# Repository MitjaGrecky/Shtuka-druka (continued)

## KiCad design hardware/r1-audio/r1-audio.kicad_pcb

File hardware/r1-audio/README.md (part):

# R1 - Audio board (rear wall, left: Audio Out and Audio In blocks)

The audio jacks and the analog front end. Every input leaves R1 as a differential pair scaled to the converters' full scale;
the Cirrus buffers around ADC_VMID / DAC_VMID (AN0635 for the CS5304P/8P inputs, AN0679 for the CS4308P outputs) sit next to the
converters on A1. Research: `docs/ru/34_rear_boards_research.md` (sections 2, 3), doc 28. Decisions: R64-R66, R72, R88,
R116-R118, R135-R137, R142 (jack positions = 3D model).

**Rev 1.4 (25.11.2026, P154):** "to F1" PH 3 -> 5 pins (DET_HP1/2), new PH-3 "HP detect to R2".
**Status: rev 1.3 (20.11.2026) - schematic and placed board, not routed; decision P114 (20.11.2026): 6 layers (F sig / In1 GND / In2 sig / In3 sig / In4 GND / B sig), generator change pending, pin rule not yet applied; changes in the Rev sections below.** Rev 0.8 (18.11.2026): 452 parts, 264 nets; Mic/Line attenuator relays since rev 0.3, user decision on В16). Levels and values checked against the datasheets (cloud task #24).

## Channels

| Input | Jack | Path | ADC (A1) |
|---|---|---|---|
| Mic/Line 1-2 | Neutrik NCJ6FI-V combo, vertical (not at JLC: hand soldering, P122; the LCSC number is outdated) | phantom 6.81k + 47 uF on XLR only (R72); TRS joins after the caps; clamps to +-12 V; relay attenuator -12 dB (rev 0.3); OPA1612 two-op-amp front end x 4.01; OPA1637 loud x 0.681 (FS +11.9 dBu) and quiet x 68.1 (+40 dB, FS -28.1 dBu) | 1-4 (two per input, R117) |
| Hi-Z 1-2 | Neutrik NJ3FD-V, vertical | 1 MOhm, clamps, OPA1642 buffer; OPA1637 loud x 1.37 (FS +17.9 dBu), quiet x 137 (+40 dB, FS -22.1 dBu) | 5-8 |
| Phono L/R | RCA with nut (part to choose) | relay per channel (R118; off = line): line -> OPA1637 x 4.12 (FS +8.3 dBu); phono -> computed RIAA on OPA1612 (+35 dB at 1 kHz) -> OPA1637 x 4.12 | 9-10 |
| Line 1-8 | NJ3FD-V | RF filter, OPA1637 diff x 0.674: FS +24.1 dBu (R135) | 11-18 |
| Spare (R88) | - | on A1 | 19-20 |

| Output | Path |
|---|---|
| Main L/R, Aux L/R (NJ3FD-V) | DAC pair (2 Vrms diff from the A1 I-V stage) -> OPA1612 difference amp x 3.09 -> 6.19 Vrms = +18.0 dBu (R64); hot through 47 R, cold 47 R to GND (impedance-balanced) |
| RCA L/R | copy of Main through 100 R (R23) |
| Relays | Omron G6K-2F-Y 5 V, one DPDT per pair (Main, Aux, RCA): normally open, close only when MUTE and R2_OK are high (R66, R137, R118) |

Phantom per channel (R118): MMBTA92 (300 V PNP) high-side switch from +48 V, slow ramp by a Miller capacitor (2.2 uF base-collector), driven from R2 through an
MMBTA42 (300 V NPN, the collector sees 48 V); 47k bleeder.

Connectors: power from PW (Micro-Fit 2x5, same pinout as PW "to A1/R1"), control from R2 (2x7: the 2x5 pinout of R2 "to A1/R1" plus ATT1 at pin 11 and ATT2 at pin 13, GND between; R2 must be widened - PC task #25),
to A1: 2x20 (ADC 1-10) and 2x25 (ADC 11-18, DAC 1-4, +-12 V, +5 V) - pairs on adjacent pins with GND pairs between.

## Level plan (checked, rev 0.2)

Sources: CS53A04P datasheet DS1397 (same family as CS5304P/8P), CS4308P DS1317, Cirrus AN0635 and AN0679.

- **ADC:** 0 dBFS = 2.0 Vrms differential at the ADC pins (scales with VDD_A). The recommended AN0635 input buffer (inverting, 1.2k in /
  300 R feedback, 68 uF per leg, OPA1612) has gain 1/4: 0 dBFS = **8 Vrms differential** at the buffer. Rev 0.1 assumed 2 Vrms - every
  gain is now x 4.17 higher. With the 49.9 R build-out the R1 driver must deliver 8.33 Vrms differential at full scale.
  The 49.9 R + 1 nF filter: 1.6 MHz differential, fine ahead of the buffer's own 640 kHz filter; C0G.
- **Line 1-8:** gain 6.81k / (10k + 100 R) = 0.674, FS at +24.1 dBu (R135). Input 100 R + 1 nF (RF, 1.6 MHz). No clamps (a clamp to +-12 V
  would clip +24 dBu = 17 Vpk); the OPA1637 inputs see only the Rg current.
- **Mic/Line:** front end 1 + 2 x 499 / 332 = 4.01 (+12 dB) - the 332 R gives thermal noise 2.3 nV/rtHz instead of 3.3 with 665 R. The front end clips at
  about +13.6 dBu (+-10.5 V on each output), so FS of the loud path is set to +11.9 dBu: **no pad is needed**, the loud path has 1.7 dB headroom
  over line level; a line signal above +13.6 dBu on the combo clips (question to the user). Quiet path +40 dB higher, FS -28.1 dBu; the 1k Rg
  keeps the fault current into the OPA1637 below 10 mA.
- **Attenuator (rev 0.3, В16 b):** one G6K-2F-Y per combo after the phantom caps and the 10 R, in front of the clamps and the front end: 15k series + 4.99k shunt per leg
  (ratio 0.250 = -12.0 dB, 0.1 %). De-energised = direct (mic), energised = attenuated: FS of the loud path +23.9 dBu; the clamps see
  only the attenuated signal. Control: ATT1/ATT2 from R2 (3.3 V) through a 2N7002, flyback diode per coil. In the direct position the divider loads each leg with 20k
  (parallel to the 10k bias: 6.7k per leg, 13 k differential) - fine for microphones; the divider adds 7.8 nV/rtHz only while attenuated.
- **Hi-Z:** OPA1642 buffer, then x 1.37 / x 137 (FS +17.9 / -22.1 dBu). The JFET buffer keeps the 1 MOhm input.
- **Phono:** FS of the line path +8.3 dBu (2.02 Vrms, CD level). RIAA computed (script in the cloud task, `docs/ru/` note): active stage 3180 / 318 us
  (68.1k || 47n in series with 7.42k, over 130 R + 470 uF), 75 us as a passive section 787 R + 100 nF ahead of the FDA (input 16.7 k).
  Gain +35.0 dB at 1 kHz, **error below 0.05 dB from 20 Hz to 20 kHz** (nominal values), FS 36 mV at 1 kHz (7 x the 5 mV of a normal MM
  cartridge); corner of the 130 R + 470 uF leg 2.6 Hz (the subsonic rolloff is left to the DSP). 0.1 % resistors and 1 % C0G capacitors give
  about +-0.1 dB.
- **Outputs:** CS4308P current-mode output 1.67 mA rms (1.63-1.71) per channel; AN0679 I-V stage 1.2 kOhm gives 2.0 Vrms differential
  (the A1 stage, not R1). R1: x 3.09 -> 6.19 Vrms = +18.0 dBu per channel, impedance-balanced (cold 47 R).
- **Phantom:** MMBTA92 + Miller capacitor 2.2 uF between base and collector: base current 0.45 mA from the 100k, ramp about 0.1-0.2 s
  (X7R loses capacity at 48 V, 1-2 uF effective); Vce(sat) < 0.5 V at 14 mA (both legs shorted); turn-off through the 100k pull-up
  and the 47k bleeder. Estimated, not simulated. The level shifter is the MMBTA42 (300 V): the old MMBT3904 (40 V) sees 48 V on its
  collector when off.

## Still open

- Mic EIN: front end 2.3 nV/rtHz plus the 6.81k phantom resistors (about 3.3 nV/rtHz each in parallel to the capsule) - about -125 dBu EIN estimated,
  to measure on the first board; the quiet path reaches ADC FS at -28.1 dBu, so the ADC noise floor (123 dBA) is -95 dBu referred to the input.
- Jack mechanics: vertical-mount NCJ6FI-V and NJ3FD-V on a vertical board; RCA part; positions from the 3D model.
- Model vs R118: the model shows a Phono/Line switch on the wall, R118 says R2 switches phono/line (relays here).
- The A1 buffers (AN0635, AN0679) are on A1: R1 only assumes them.

Rev 0.4 (14.11.2026, PC): JST PH 3 "to F1 (mute)" with MUTE, R2_OK, GND for the headphone board.

Checks: `tools/sch_netcheck.py hardware/r1-audio` - 440 symbol units, 1159 pins, 0 mismatches; every symbol pin listed.
ERC by CI. OPA1637 symbol: project library (`hardware/m1-screen-knobs/gen/make_lib.py`, `opa1637()`).

Generators: `gen/design.py`, `gen/make_sch.py`. On the PC set `KICAD_SYMBOL_DIR=<repo>/hardware/common/sym7`.

License: CERN-OHL-S-2.0 (hardware), AGPL-3.0-or-later (scripts).

## Rev 0.5: placed board for routing (14.11.2026, PC)
Placed board (no routing) generated by `gen/make_pcb.py`; `UNROUTED` marker for CI; package `hardware/for-routing/R1`. Placement is a starting point: jacks at the 3D-model positions, the rest by `hardware/common/gen/autoplace.py` (ICs on a grid, small parts around the IC they share signals with, cable headers along the bottom edge). Outline and mounting holes are rough until the enclosure is fixed. `pcb_geomcheck`: 0 problems.

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
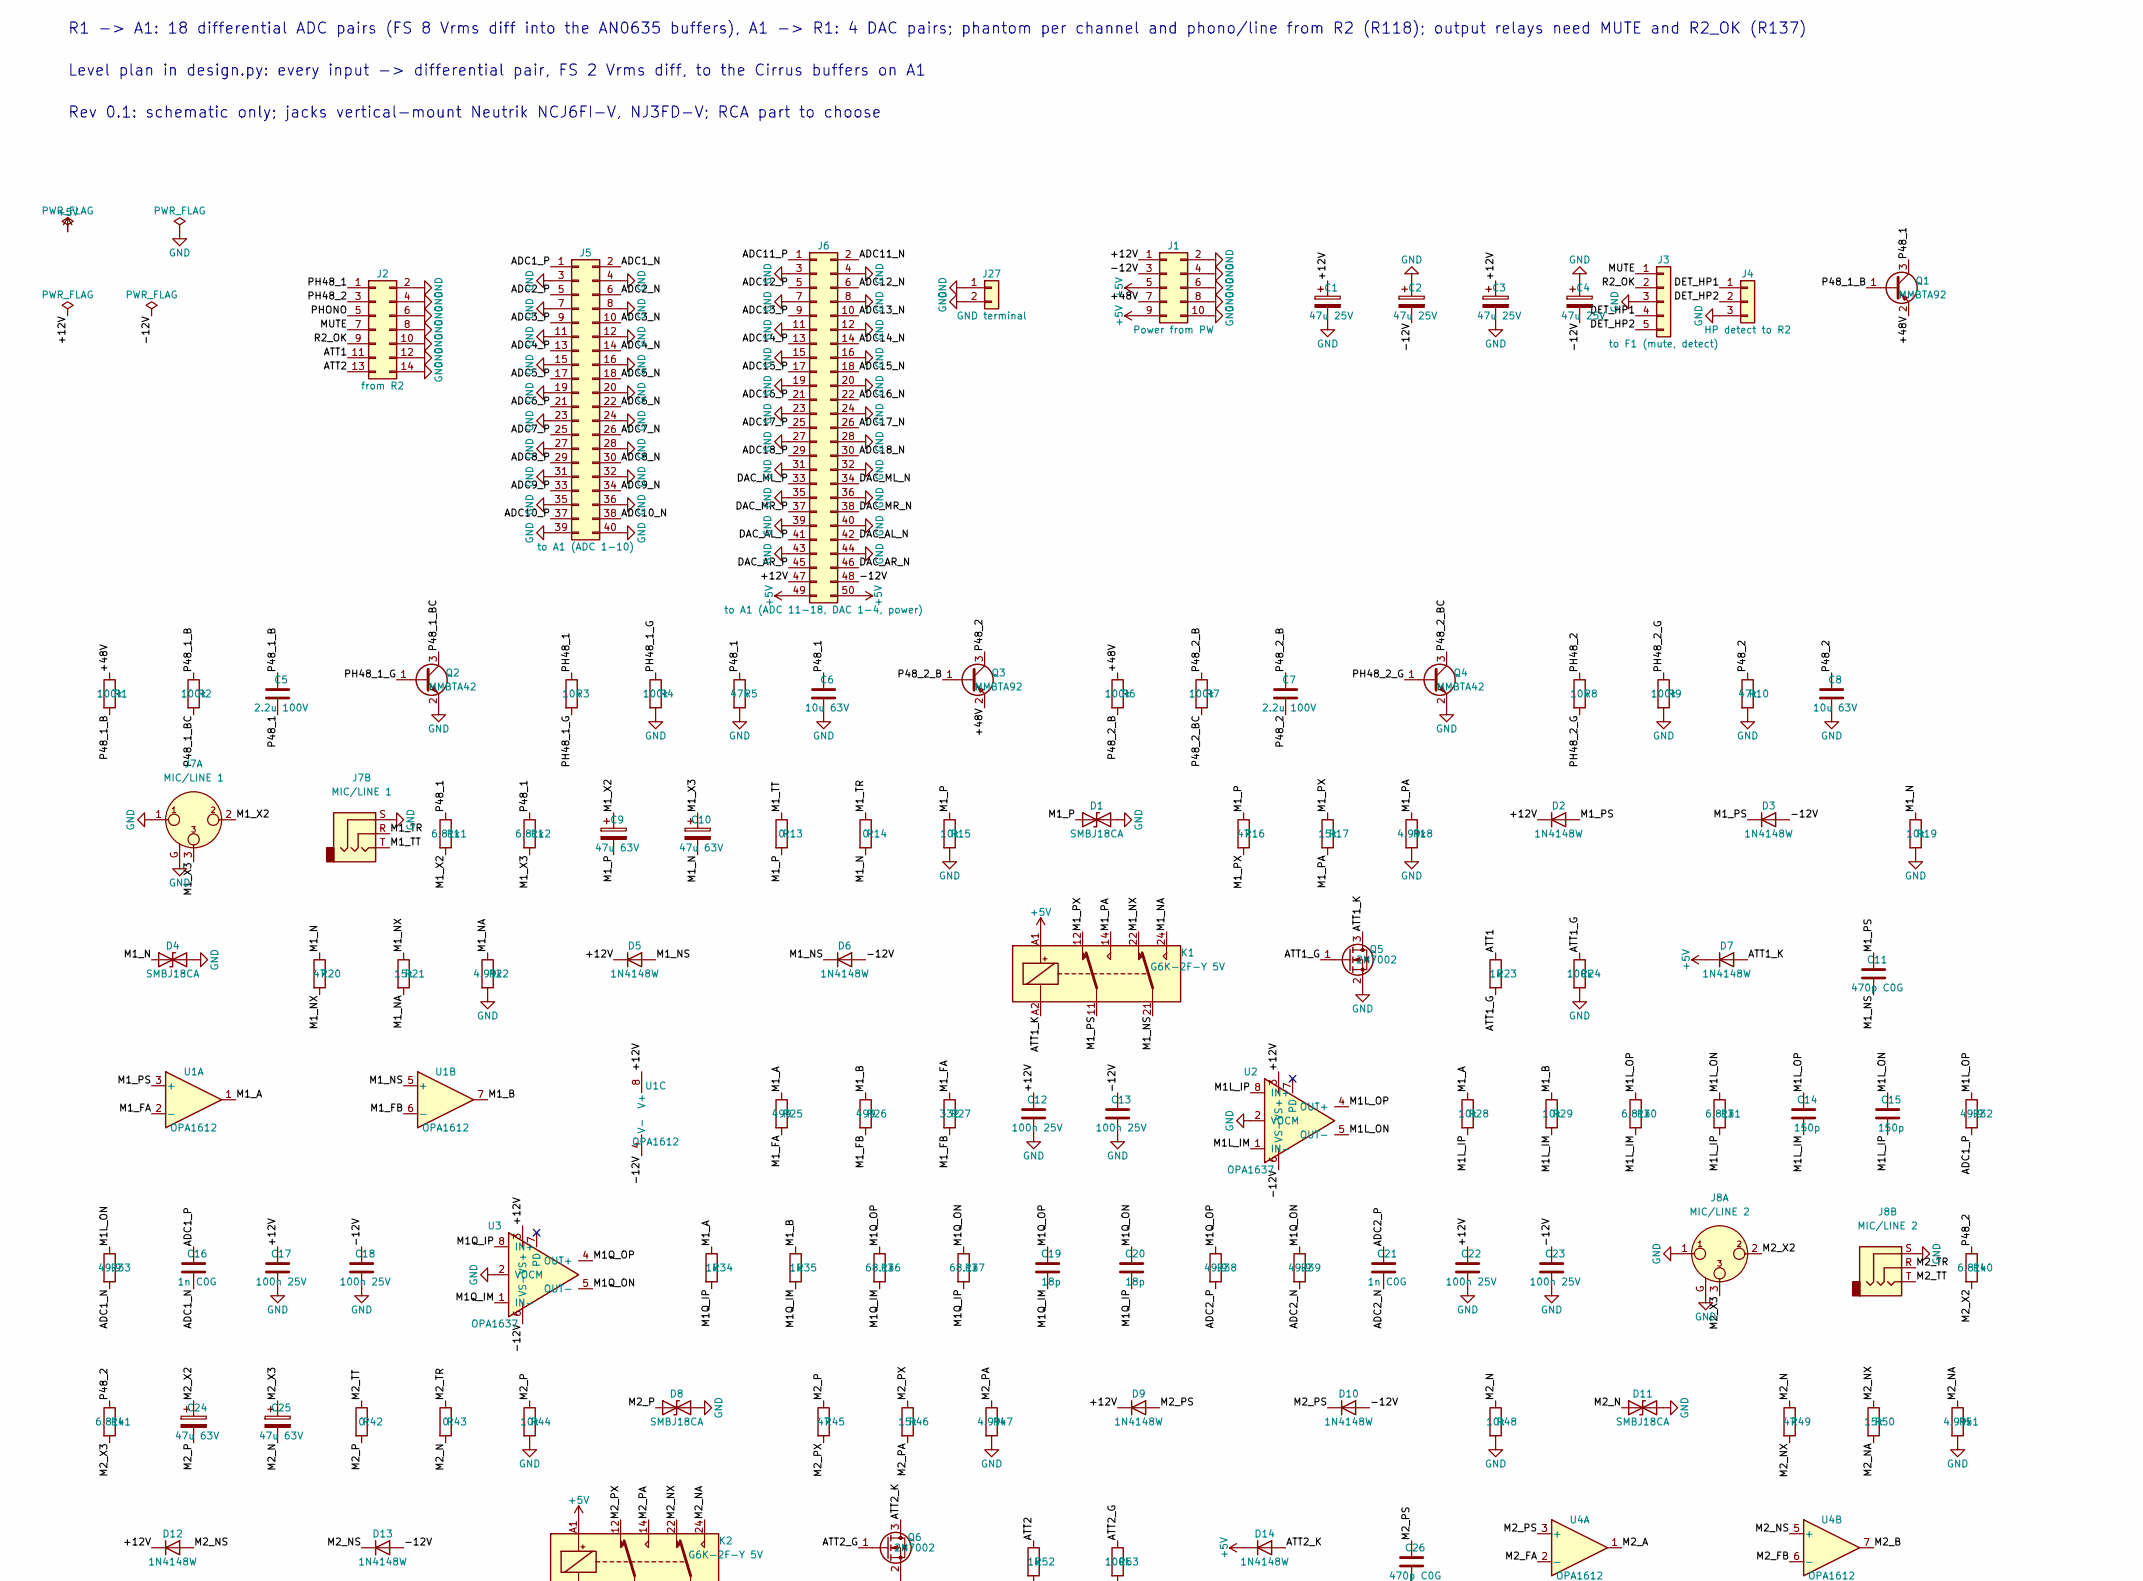
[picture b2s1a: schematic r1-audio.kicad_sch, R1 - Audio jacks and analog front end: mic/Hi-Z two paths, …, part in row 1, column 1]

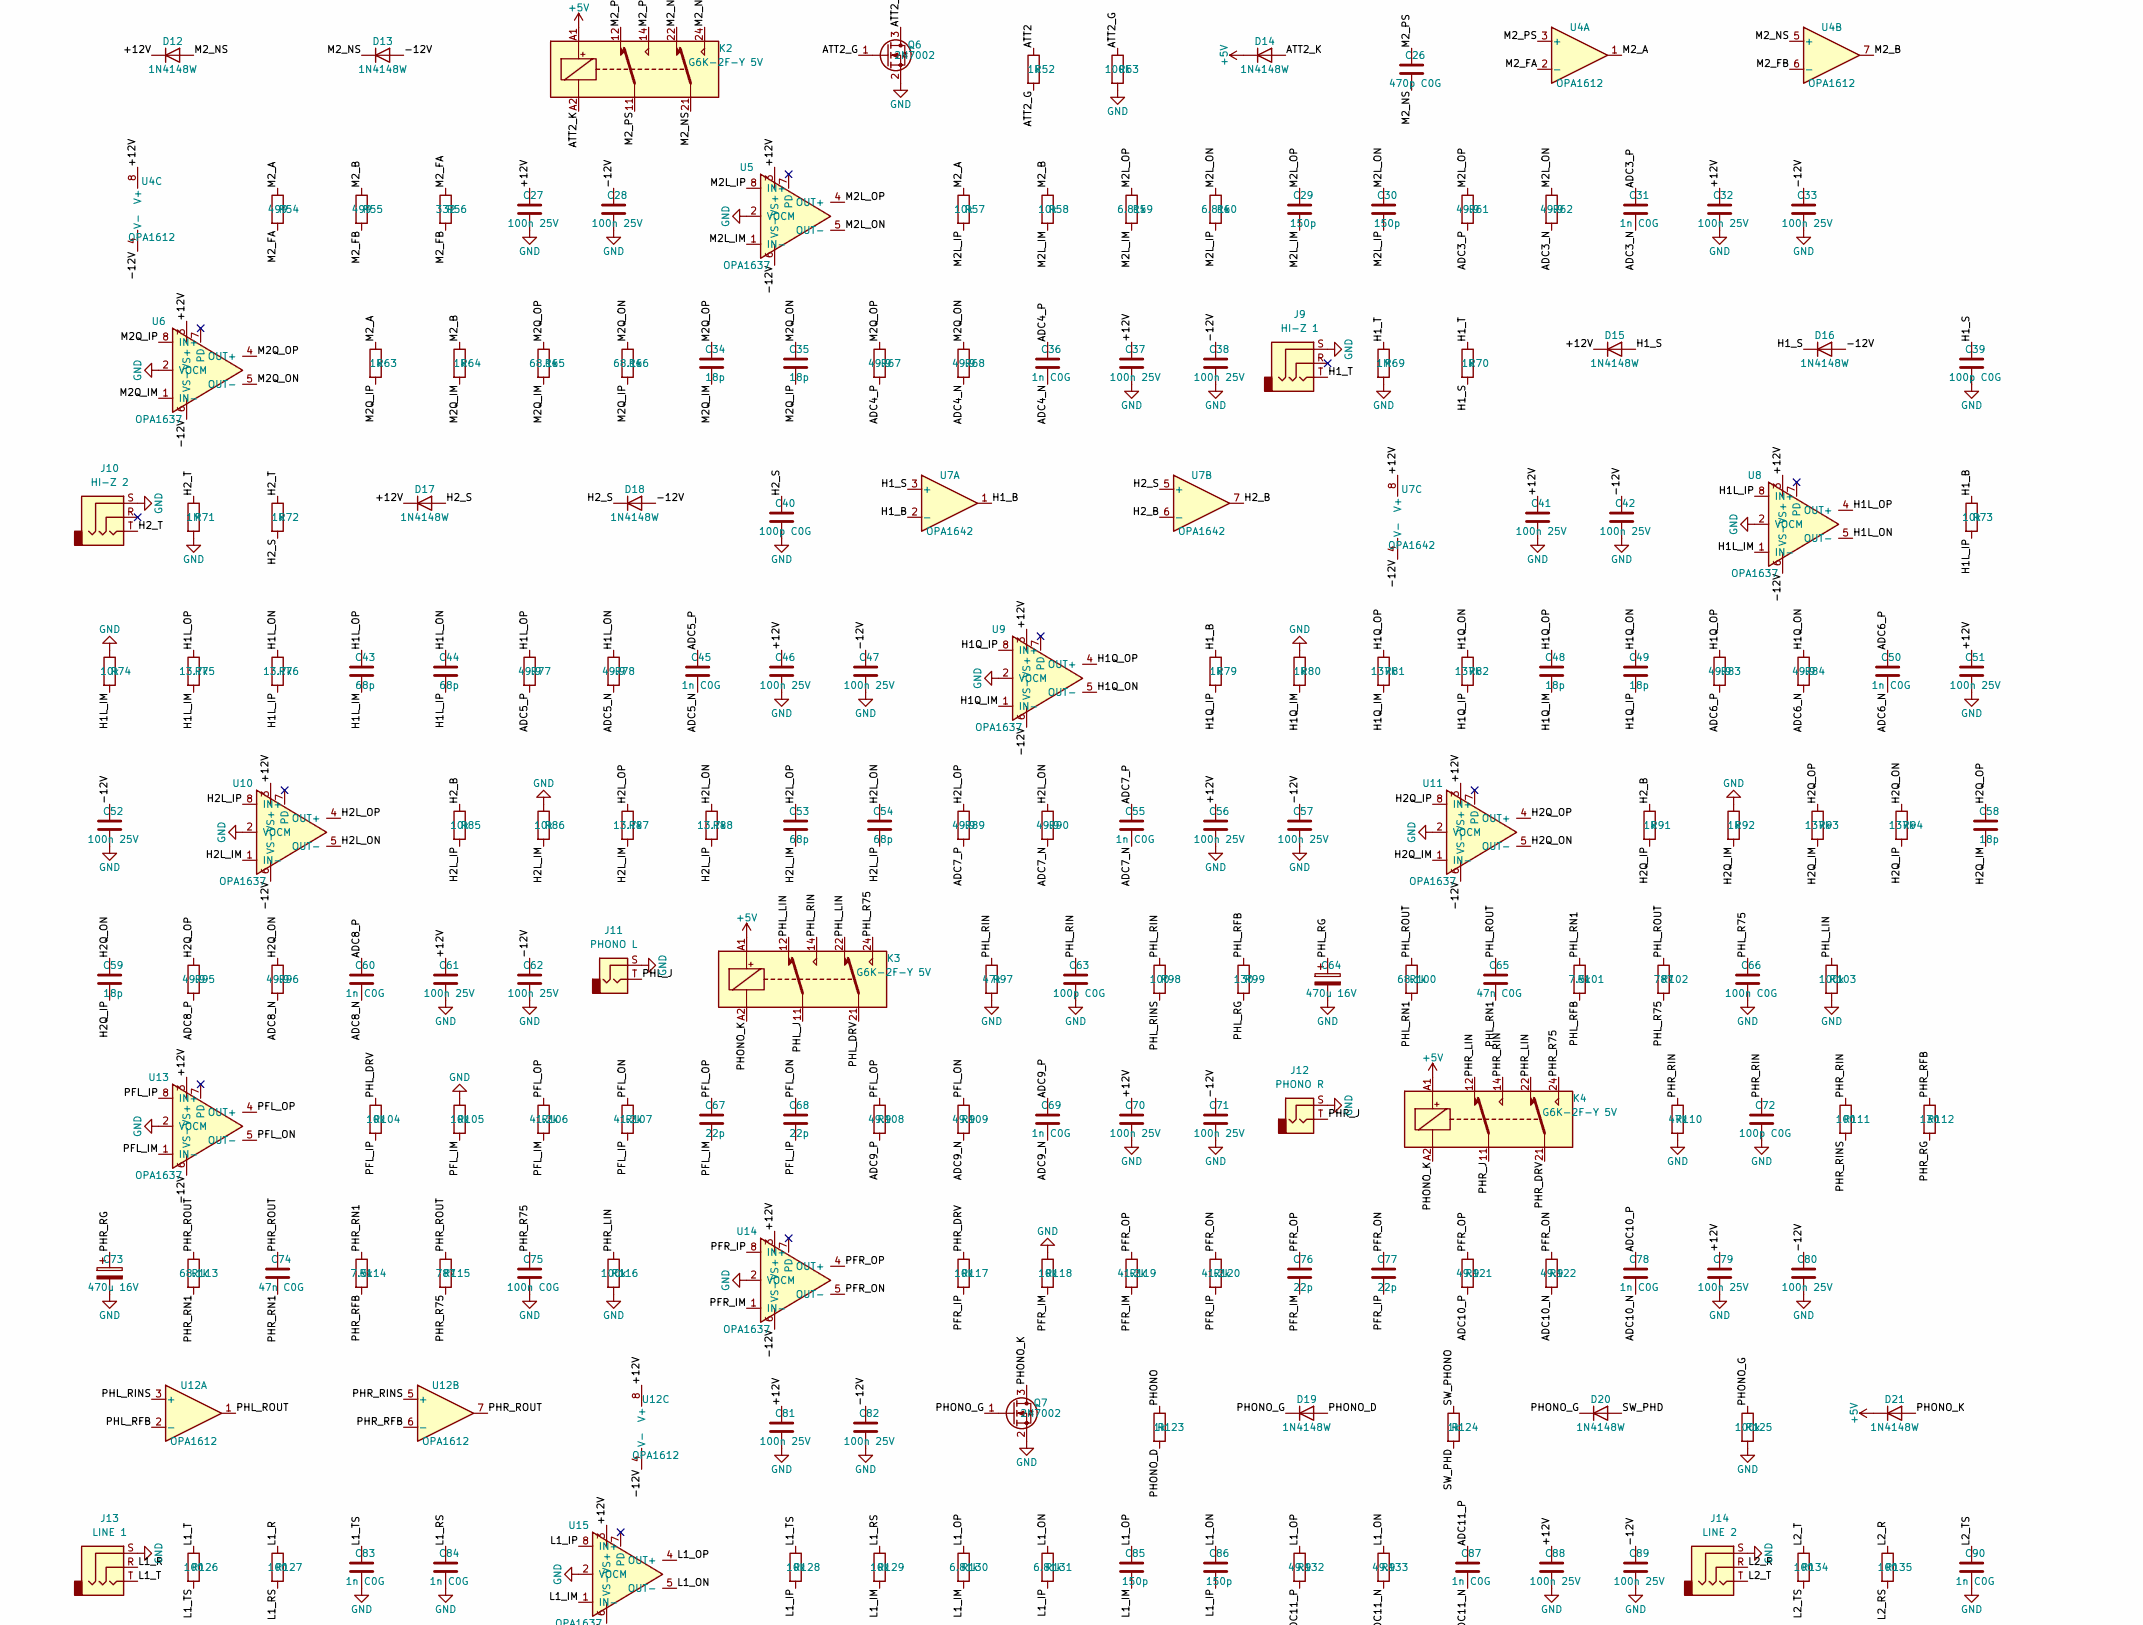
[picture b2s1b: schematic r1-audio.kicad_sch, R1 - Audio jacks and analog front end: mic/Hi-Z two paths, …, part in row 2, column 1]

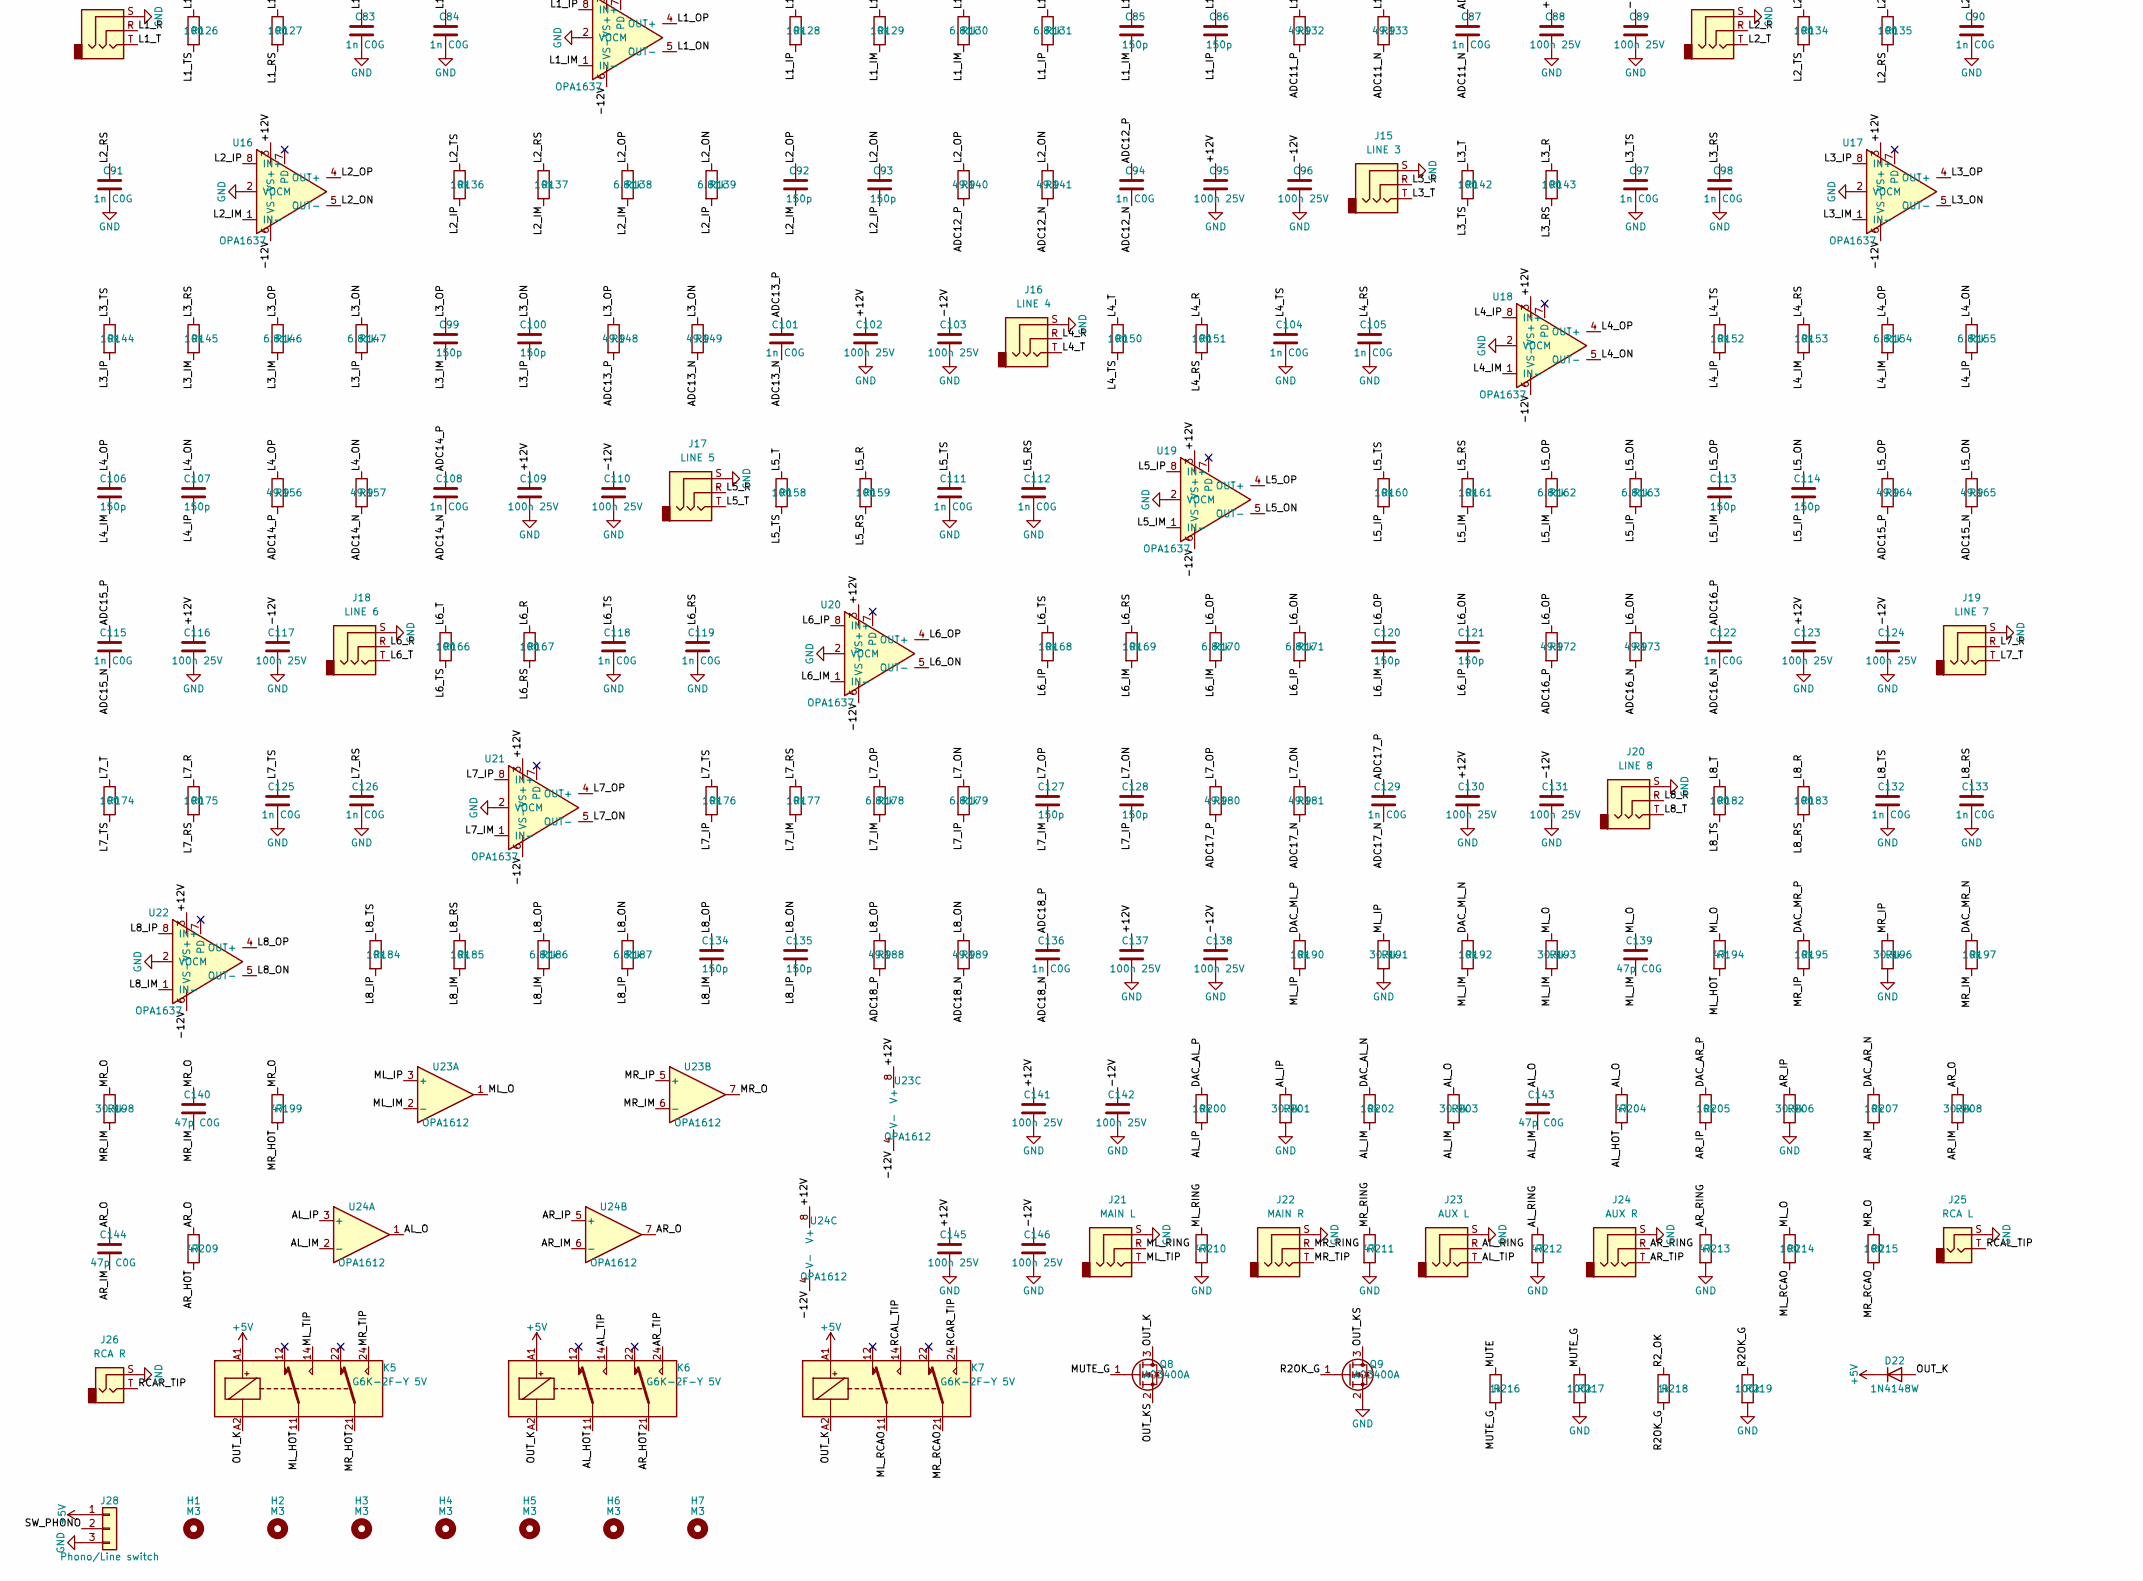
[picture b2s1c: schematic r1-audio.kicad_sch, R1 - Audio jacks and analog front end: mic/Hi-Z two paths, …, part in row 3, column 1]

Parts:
C1, C2, C3, C4: 47u 25V; CP_Elec_6.3x7.7
C5, C7: 2.2u 100V; C_1210_3225Metric
C6, C8: 10u 63V; C_1210_3225Metric
C9, C10, C24, C25: 47u 63V; CP_Elec_8x10.5
C11, C26: 470p C0G; C_0603_1608Metric
C12, C13, C17, C18, C22, C23, C27, C28, C32, C33, C37, C38, C41, C42, C46, C47, C51, C52, C56, C57, C61, C62, C70, C71, C79, C80, C81, C82, C88, C89, C95, C96, C102, C103, C109, C110, C116, C117, C123, C124, C130, C131, C137, C138, C141, C142, C145, C146: 100n 25V; C_0603_1608Metric
C14, C15, C29, C30, C85, C86, C92, C93, C99, C100, C106, C107, C113, C114, C120, C121, C127, C128, C134, C135: 150p; C_0603_1608Metric
C16, C21, C31, C36, C45, C50, C55, C60, C69, C78, C83, C84, C87, C90, C91, C94, C97, C98, C101, C104, C105, C108, C111, C112, C115, C118, C119, C122, C125, C126, C129, C132, C133, C136: 1n C0G; C_0603_1608Metric
C19, C20, C34, C35, C48, C49, C58, C59: 18p; C_0603_1608Metric
C39, C40, C63, C72: 100p C0G; C_0603_1608Metric
C43, C44, C53, C54: 68p; C_0603_1608Metric
C64, C73: 470u 16V; CP_Elec_8x10.5
C65, C74: 47n C0G; C_1206_3216Metric
C66, C75: 100n C0G; C_1206_3216Metric
C67, C68, C76, C77: 22p; C_0603_1608Metric
C139, C140, C143, C144: 47p C0G; C_0603_1608Metric
D1, D4, D8, D11: SMBJ18CA; D_SMB; LCSC C83327
D2, D3, D5, D6, D7, D9, D10, D12, D13, D14, D15, D16, D17, D18, D19, D20, D21, D22: 1N4148W; D_SOD-123
H1, H2, H3, H4, H5, H6, H7: M3; MountingHole_3.2mm_M3_ISO7380
J1: Power from PW; Molex_Micro-Fit_3.0_43045-1012_2x05_P3.00mm_Vertical; LCSC C277725
J2: from R2; PinHeader_2x07_P2.54mm_Vertical
J3: to F1 (mute, detect); JST_PH_B5B-PH-K_1x05_P2.00mm_Vertical; LCSC C157993
J4: HP detect to R2; JST_PH_B3B-PH-K_1x03_P2.00mm_Vertical; LCSC C131339
J5: to A1 (ADC 1-10); PinHeader_2x20_P2.54mm_Vertical
J6: to A1 (ADC 11-18, DAC 1-4, power); PinHeader_2x25_P2.54mm_Vertical
J7: MIC/LINE 1; Jack_XLR-6.35mm_Neutrik_NCJ6FI-V_Vertical; LCSC C368503
J8: MIC/LINE 2; Jack_XLR-6.35mm_Neutrik_NCJ6FI-V_Vertical; LCSC C368503
J9: HI-Z 1; Jack_6.35mm_Neutrik_NJ3FD-V_Vertical
J10: HI-Z 2; Jack_6.35mm_Neutrik_NJ3FD-V_Vertical
J11: PHONO L; Jack_RCA_SameSky_RCJ-02_Vertical; LCSC C4991609
J12: PHONO R; Jack_RCA_SameSky_RCJ-02_Vertical; LCSC C4991609
J13: LINE 1; Jack_6.35mm_Neutrik_NJ3FD-V_Vertical
J14: LINE 2; Jack_6.35mm_Neutrik_NJ3FD-V_Vertical
J15: LINE 3; Jack_6.35mm_Neutrik_NJ3FD-V_Vertical
J16: LINE 4; Jack_6.35mm_Neutrik_NJ3FD-V_Vertical
J17: LINE 5; Jack_6.35mm_Neutrik_NJ3FD-V_Vertical
J18: LINE 6; Jack_6.35mm_Neutrik_NJ3FD-V_Vertical
J19: LINE 7; Jack_6.35mm_Neutrik_NJ3FD-V_Vertical
J20: LINE 8; Jack_6.35mm_Neutrik_NJ3FD-V_Vertical
J21: MAIN L; Jack_6.35mm_Neutrik_NJ3FD-V_Vertical
J22: MAIN R; Jack_6.35mm_Neutrik_NJ3FD-V_Vertical
J23: AUX L; Jack_6.35mm_Neutrik_NJ3FD-V_Vertical
J24: AUX R; Jack_6.35mm_Neutrik_NJ3FD-V_Vertical
J25: RCA L; Jack_RCA_SameSky_RCJ-02_Vertical; LCSC C4991609
J26: RCA R; Jack_RCA_SameSky_RCJ-02_Vertical; LCSC C4991609
J27: GND terminal; JST_PH_B2B-PH-K_1x02_P2.00mm_Vertical; LCSC C131337
J28: Phono/Line switch; JST_PH_B3B-PH-K_1x03_P2.00mm_Vertical; LCSC C131339
K1, K2, K3, K4, K5, K6, K7: G6K-2F-Y 5V; Relay_DPDT_Omron_G6K-2F-Y; LCSC C2982926
Q1, Q3: MMBTA92; SOT-23; LCSC C3009890
Q2, Q4: MMBTA42; SOT-23
Q5, Q6, Q7: 2N7002; SOT-23
Q8, Q9: AO3400A; SOT-23; LCSC C20917
R1, R2, R4, R6, R7, R9, R24, R53, R103, R116, R125, R217, R219: 100k; R_0402_1005Metric
R3, R8, R15, R19, R28, R29, R44, R48, R57, R58, R73, R74, R85, R86, R104, R105, R117, R118, R128, R129, R136, R137, R144, R145, R152, R153, R160, R161, R168, R169, R176, R177, R184, R185, R190, R192, R195, R197, R200, R202, R205, R207: 10k; R_0402_1005Metric
R5, R10: 47k; R_0603_1608Metric
R11, R12, R40, R41: 6.81k; R_1206_3216Metric
R13, R14, R42, R43: 0; R_0402_1005Metric
R16, R20, R45, R49: 47; R_0805_2012Metric; LCSC C17714
R17, R21, R46, R50: 15k; R_0603_1608Metric
R18, R22, R47, R51: 4.99k; R_0603_1608Metric
R23, R34, R35, R52, R63, R64, R79, R80, R91, R92, R123, R124, R216, R218: 1k; R_0402_1005Metric
R25, R26, R54, R55: 499; R_0402_1005Metric
R27, R56: 332; R_0402_1005Metric
R30, R31, R59, R60, R130, R131, R138, R139, R146, R147, R154, R155, R162, R163, R170, R171, R178, R179, R186, R187: 6.81k; R_0402_1005Metric
R32, R33, R38, R39, R61, R62, R67, R68, R77, R78, R83, R84, R89, R90, R95, R96, R108, R109, R121, R122, R132, R133, R140, R141, R148, R149, R156, R157, R164, R165, R172, R173, R180, R181, R188, R189: 49.9; R_0402_1005Metric
R36, R37, R65, R66, R100, R113: 68.1k; R_0402_1005Metric
R69, R71: 1M; R_0402_1005Metric
R70, R72: 1k; R_0603_1608Metric
R75, R76, R87, R88: 13.7k; R_0402_1005Metric
R81, R82, R93, R94: 137k; R_0402_1005Metric
R97, R110: 47k; R_0402_1005Metric
R98, R111, R126, R127, R134, R135, R142, R143, R150, R151, R158, R159, R166, R167, R174, R175, R182, R183, R214, R215: 100; R_0603_1608Metric
R99, R112: 130; R_0402_1005Metric
R101, R114: 7.5k; R_0402_1005Metric; LCSC C25918
R102, R115: 787; R_0603_1608Metric
R106, R107, R119, R120: 41.2k; R_0402_1005Metric
R191, R193, R196, R198, R201, R203, R206, R208: 30.9k; R_0402_1005Metric
R194, R199, R204, R209, R210, R211, R212, R213: 47; R_0603_1608Metric
U1, U4, U12, U23, U24: OPA1612; SOIC-8_3.9x4.9mm_P1.27mm; LCSC C94590
U2, U3, U5, U6, U8, U9, U10, U11, U13, U14, U15, U16, U17, U18, U19, U20, U21, U22: OPA1637; VSSOP-8_3x3mm_P0.65mm; LCSC C2860968
U7: OPA1642; SOIC-8_3.9x4.9mm_P1.27mm; LCSC C67640

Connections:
+5V: D7.1 (K), D14.1 (K), D21.1 (K), D22.1 (K), J1.5, J1.9, J6.49, J6.50, J28.1, K1.A1, K2.A1, K3.A1, K4.A1, K5.A1, K6.A1, K7.A1
/+12V: C1.1, C3.1, C12.1, C17.1, C22.1, C27.1, C32.1, C37.1, C41.1, C46.1, C51.1, C56.1, C61.1, C70.1, C79.1, C81.1, C88.1, C95.1, C102.1, C109.1, C116.1, C123.1, C130.1, C137.1, C141.1, C145.1, D2.1 (K), D5.1 (K), D9.1 (K), D12.1 (K), D15.1 (K), D17.1 (K), J1.1, J6.47, U1.8 (V+), U2.3 (VS+), U3.3 (VS+), U4.8 (V+), U5.3 (VS+), U6.3 (VS+), U7.8 (V+), U8.3 (VS+), U9.3 (VS+), U10.3 (VS+), U11.3 (VS+), U12.8 (V+), U13.3 (VS+), U14.3 (VS+), U15.3 (VS+), U16.3 (VS+), U17.3 (VS+), U18.3 (VS+), U19.3 (VS+), U20.3 (VS+), U21.3 (VS+), U22.3 (VS+), U23.8 (V+), U24.8 (V+)
/+48V: J1.7, Q1.2 (E), Q3.2 (E), R1.1, R6.1
/-12V: C2.2, C4.2, C13.1, C18.1, C23.1, C28.1, C33.1, C38.1, C42.1, C47.1, C52.1, C57.1, C62.1, C71.1, C80.1, C82.1, C89.1, C96.1, C103.1, C110.1, C117.1, C124.1, C131.1, C138.1, C142.1, C146.1, D3.2 (A), D6.2 (A), D10.2 (A), D13.2 (A), D16.2 (A), D18.2 (A), J1.3, J6.48, U1.4 (V-), U2.6 (VS-), U3.6 (VS-), U4.4 (V-), U5.6 (VS-), U6.6 (VS-), U7.4 (V-), U8.6 (VS-), U9.6 (VS-), U10.6 (VS-), U11.6 (VS-), U12.4 (V-), U13.6 (VS-), U14.6 (VS-), U15.6 (VS-), U16.6 (VS-), U17.6 (VS-), U18.6 (VS-), U19.6 (VS-), U20.6 (VS-), U21.6 (VS-), U22.6 (VS-), U23.4 (V-), U24.4 (V-)
/ADC1_N: C16.2, J5.2, R33.2
/ADC1_P: C16.1, J5.1, R32.2
/ADC2_N: C21.2, J5.6, R39.2
/ADC2_P: C21.1, J5.5, R38.2
/ADC3_N: C31.2, J5.10, R62.2
/ADC3_P: C31.1, J5.9, R61.2
/ADC4_N: C36.2, J5.14, R68.2
/ADC4_P: C36.1, J5.13, R67.2
/ADC5_N: C45.2, J5.18, R78.2
/ADC5_P: C45.1, J5.17, R77.2
/ADC6_N: C50.2, J5.22, R84.2
/ADC6_P: C50.1, J5.21, R83.2
/ADC7_N: C55.2, J5.26, R90.2
/ADC7_P: C55.1, J5.25, R89.2
/ADC8_N: C60.2, J5.30, R96.2
/ADC8_P: C60.1, J5.29, R95.2
/ADC9_N: C69.2, J5.34, R109.2
/ADC9_P: C69.1, J5.33, R108.2
/ADC10_N: C78.2, J5.38, R122.2
/ADC10_P: C78.1, J5.37, R121.2
/ADC11_N: C87.2, J6.2, R133.2
/ADC11_P: C87.1, J6.1, R132.2
/ADC12_N: C94.2, J6.6, R141.2
/ADC12_P: C94.1, J6.5, R140.2
/ADC13_N: C101.2, J6.10, R149.2
/ADC13_P: C101.1, J6.9, R148.2
/ADC14_N: C108.2, J6.14, R157.2
/ADC14_P: C108.1, J6.13, R156.2
/ADC15_N: C115.2, J6.18, R165.2
/ADC15_P: C115.1, J6.17, R164.2
/ADC16_N: C122.2, J6.22, R173.2
/ADC16_P: C122.1, J6.21, R172.2
/ADC17_N: C129.2, J6.26, R181.2
/ADC17_P: C129.1, J6.25, R180.2
/ADC18_N: C136.2, J6.30, R189.2
/ADC18_P: C136.1, J6.29, R188.2
/AL_HOT: K6.11, R204.2
/AL_IM: C143.2, R202.2, R203.2, U24.2 (-)
/AL_IP: R200.2, R201.1, U24.3 (+)
/AL_O: C143.1, R203.1, R204.1, U24.1
/AL_RING: J23.R, R212.1
/AL_TIP: J23.T, K6.14
/AR_HOT: K6.21, R209.2
/AR_IM: C144.2, R207.2, R208.2, U24.6 (-)
/AR_IP: R205.2, R206.1, U24.5 (+)
/AR_O: C144.1, R208.1, R209.1, U24.7
/AR_RING: J24.R, R213.1
/AR_TIP: J24.T, K6.24
/ATT1: J2.11, R23.1
/ATT1_G: Q5.1 (G), R23.2, R24.1
/ATT1_K: D7.2 (A), K1.A2, Q5.3 (D)
/ATT2: J2.13, R52.1
/ATT2_G: Q6.1 (G), R52.2, R53.1
/ATT2_K: D14.2 (A), K2.A2, Q6.3 (D)
/DAC_AL_N: J6.42, R202.1
/DAC_AL_P: J6.41, R200.1
/DAC_AR_N: J6.46, R207.1
/DAC_AR_P: J6.45, R205.1
/DAC_ML_N: J6.34, R192.1
/DAC_ML_P: J6.33, R190.1
/DAC_MR_N: J6.38, R197.1
/DAC_MR_P: J6.37, R195.1
/DET_HP1: J3.4, J4.1
/DET_HP2: J3.5, J4.2
/H1L_IM: C43.2, R74.2, R75.2, U8.1 (IN-)
/H1L_IP: C44.2, R73.2, R76.2, U8.8 (IN+)
/H1L_ON: C44.1, R76.1, R78.1, U8.5 (OUT-)
/H1L_OP: C43.1, R75.1, R77.1, U8.4 (OUT+)
/H1Q_IM: C48.2, R80.2, R81.2, U9.1 (IN-)
/H1Q_IP: C49.2, R79.2, R82.2, U9.8 (IN+)
/H1Q_ON: C49.1, R82.1, R84.1, U9.5 (OUT-)
/H1Q_OP: C48.1, R81.1, R83.1, U9.4 (OUT+)
/H1_B: R73.1, R79.1, U7.1, U7.2 (-)
/H1_S: C39.1, D15.2 (A), D16.1 (K), R70.2, U7.3 (+)
/H1_T: J9.T, R69.1, R70.1
/H2L_IM: C53.2, R86.2, R87.2, U10.1 (IN-)
/H2L_IP: C54.2, R85.2, R88.2, U10.8 (IN+)
/H2L_ON: C54.1, R88.1, R90.1, U10.5 (OUT-)
/H2L_OP: C53.1, R87.1, R89.1, U10.4 (OUT+)
/H2Q_IM: C58.2, R92.2, R93.2, U11.1 (IN-)
/H2Q_IP: C59.2, R91.2, R94.2, U11.8 (IN+)
/H2Q_ON: C59.1, R94.1, R96.1, U11.5 (OUT-)
/H2Q_OP: C58.1, R93.1, R95.1, U11.4 (OUT+)
/H2_B: R85.1, R91.1, U7.6 (-), U7.7
/H2_S: C40.1, D17.2 (A), D18.1 (K), R72.2, U7.5 (+)
/H2_T: J10.T, R71.1, R72.1
/L1_IM: C85.2, R129.2, R130.2, U15.1 (IN-)
/L1_IP: C86.2, R128.2, R131.2, U15.8 (IN+)
/L1_ON: C86.1, R131.1, R133.1, U15.5 (OUT-)
/L1_OP: C85.1, R130.1, R132.1, U15.4 (OUT+)
/L1_R: J13.R, R127.1
/L1_RS: C84.1, R127.2, R129.1
/L1_T: J13.T, R126.1
/L1_TS: C83.1, R126.2, R128.1
/L2_IM: C92.2, R137.2, R138.2, U16.1 (IN-)
/L2_IP: C93.2, R136.2, R139.2, U16.8 (IN+)
/L2_ON: C93.1, R139.1, R141.1, U16.5 (OUT-)
/L2_OP: C92.1, R138.1, R140.1, U16.4 (OUT+)
/L2_R: J14.R, R135.1
/L2_RS: C91.1, R135.2, R137.1
/L2_T: J14.T, R134.1
/L2_TS: C90.1, R134.2, R136.1
/L3_IM: C99.2, R145.2, R146.2, U17.1 (IN-)
/L3_IP: C100.2, R144.2, R147.2, U17.8 (IN+)
/L3_ON: C100.1, R147.1, R149.1, U17.5 (OUT-)
/L3_OP: C99.1, R146.1, R148.1, U17.4 (OUT+)
/L3_R: J15.R, R143.1
/L3_RS: C98.1, R143.2, R145.1
/L3_T: J15.T, R142.1
/L3_TS: C97.1, R142.2, R144.1
/L4_IM: C106.2, R153.2, R154.2, U18.1 (IN-)
/L4_IP: C107.2, R152.2, R155.2, U18.8 (IN+)
/L4_ON: C107.1, R155.1, R157.1, U18.5 (OUT-)
/L4_OP: C106.1, R154.1, R156.1, U18.4 (OUT+)
/L4_R: J16.R, R151.1
/L4_RS: C105.1, R151.2, R153.1
/L4_T: J16.T, R150.1
/L4_TS: C104.1, R150.2, R152.1
/L5_IM: C113.2, R161.2, R162.2, U19.1 (IN-)
/L5_IP: C114.2, R160.2, R163.2, U19.8 (IN+)
/L5_ON: C114.1, R163.1, R165.1, U19.5 (OUT-)
/L5_OP: C113.1, R162.1, R164.1, U19.4 (OUT+)
/L5_R: J17.R, R159.1
/L5_RS: C112.1, R159.2, R161.1
/L5_T: J17.T, R158.1
/L5_TS: C111.1, R158.2, R160.1
/L6_IM: C120.2, R169.2, R170.2, U20.1 (IN-)
/L6_IP: C121.2, R168.2, R171.2, U20.8 (IN+)
/L6_ON: C121.1, R171.1, R173.1, U20.5 (OUT-)
/L6_OP: C120.1, R170.1, R172.1, U20.4 (OUT+)
/L6_R: J18.R, R167.1
/L6_RS: C119.1, R167.2, R169.1
/L6_T: J18.T, R166.1
/L6_TS: C118.1, R166.2, R168.1
/L7_IM: C127.2, R177.2, R178.2, U21.1 (IN-)
/L7_IP: C128.2, R176.2, R179.2, U21.8 (IN+)
/L7_ON: C128.1, R179.1, R181.1, U21.5 (OUT-)
/L7_OP: C127.1, R178.1, R180.1, U21.4 (OUT+)
/L7_R: J19.R, R175.1
/L7_RS: C126.1, R175.2, R177.1
/L7_T: J19.T, R174.1
/L7_TS: C125.1, R174.2, R176.1
/L8_IM: C134.2, R185.2, R186.2, U22.1 (IN-)
/L8_IP: C135.2, R184.2, R187.2, U22.8 (IN+)
/L8_ON: C135.1, R187.1, R189.1, U22.5 (OUT-)
/L8_OP: C134.1, R186.1, R188.1, U22.4 (OUT+)
/L8_R: J20.R, R183.1
/L8_RS: C133.1, R183.2, R185.1
/L8_T: J20.T, R182.1
/L8_TS: C132.1, R182.2, R184.1
/M1L_IM: C14.2, R29.2, R30.2, U2.1 (IN-)
/M1L_IP: C15.2, R28.2, R31.2, U2.8 (IN+)
/M1L_ON: C15.1, R31.1, R33.1, U2.5 (OUT-)
/M1L_OP: C14.1, R30.1, R32.1, U2.4 (OUT+)
/M1Q_IM: C19.2, R35.2, R36.2, U3.1 (IN-)
/M1Q_IP: C20.2, R34.2, R37.2, U3.8 (IN+)
/M1Q_ON: C20.1, R37.1, R39.1, U3.5 (OUT-)
/M1Q_OP: C19.1, R36.1, R38.1, U3.4 (OUT+)
/M1_A: R25.1, R28.1, R34.1, U1.1
/M1_B: R26.1, R29.1, R35.1, U1.7
/M1_FA: R25.2, R27.1, U1.2 (-)
/M1_FB: R26.2, R27.2, U1.6 (-)
/M1_N: C10.2, D4.1 (A1), R14.2, R19.1, R20.1
/M1_NA: K1.24, R21.2, R22.1
/M1_NS: C11.2, D5.2 (A), D6.1 (K), K1.21, U1.5 (+)
/M1_NX: K1.22, R20.2, R21.1
/M1_P: C9.2, D1.1 (A1), R13.2, R15.1, R16.1
/M1_PA: K1.14, R17.2, R18.1
/M1_PS: C11.1, D2.2 (A), D3.1 (K), K1.11, U1.3 (+)
/M1_PX: K1.12, R16.2, R17.1
/M1_TR: J7.R, R14.1
/M1_TT: J7.T, R13.1
/M1_X2: C9.1, J7.2, R11.2
/M1_X3: C10.1, J7.3, R12.2
/M2L_IM: C29.2, R58.2, R59.2, U5.1 (IN-)
/M2L_IP: C30.2, R57.2, R60.2, U5.8 (IN+)
/M2L_ON: C30.1, R60.1, R62.1, U5.5 (OUT-)
/M2L_OP: C29.1, R59.1, R61.1, U5.4 (OUT+)
/M2Q_IM: C34.2, R64.2, R65.2, U6.1 (IN-)
/M2Q_IP: C35.2, R63.2, R66.2, U6.8 (IN+)
/M2Q_ON: C35.1, R66.1, R68.1, U6.5 (OUT-)
/M2Q_OP: C34.1, R65.1, R67.1, U6.4 (OUT+)
/M2_A: R54.1, R57.1, R63.1, U4.1
/M2_B: R55.1, R58.1, R64.1, U4.7
/M2_FA: R54.2, R56.1, U4.2 (-)
/M2_FB: R55.2, R56.2, U4.6 (-)
/M2_N: C25.2, D11.1 (A1), R43.2, R48.1, R49.1
/M2_NA: K2.24, R50.2, R51.1
/M2_NS: C26.2, D12.2 (A), D13.1 (K), K2.21, U4.5 (+)
/M2_NX: K2.22, R49.2, R50.1
/M2_P: C24.2, D8.1 (A1), R42.2, R44.1, R45.1
/M2_PA: K2.14, R46.2, R47.1
/M2_PS: C26.1, D9.2 (A), D10.1 (K), K2.11, U4.3 (+)
/M2_PX: K2.12, R45.2, R46.1
/M2_TR: J8.R, R43.1
/M2_TT: J8.T, R42.1
/M2_X2: C24.1, J8.2, R40.2
/M2_X3: C25.1, J8.3, R41.2
/ML_HOT: K5.11, R194.2
/ML_IM: C139.2, R192.2, R193.2, U23.2 (-)
/ML_IP: R190.2, R191.1, U23.3 (+)
/ML_O: C139.1, R193.1, R194.1, R214.1, U23.1
/ML_RCAO: K7.11, R214.2
/ML_RING: J21.R, R210.1
/ML_TIP: J21.T, K5.14
/MR_HOT: K5.21, R199.2
/MR_IM: C140.2, R197.2, R198.2, U23.6 (-)
/MR_IP: R195.2, R196.1, U23.5 (+)
/MR_O: C140.1, R198.1, R199.1, R215.1, U23.7
/MR_RCAO: K7.21, R215.2
/MR_RING: J22.R, R211.1
/MR_TIP: J22.T, K5.24
/MUTE: J2.7, J3.1, R216.1
/MUTE_G: Q8.1 (G), R216.2, R217.1
/OUT_K: D22.2 (A), K5.A2, K6.A2, K7.A2, Q8.3 (D)
/OUT_KS: Q8.2 (S), Q9.3 (D)
/P48_1: C5.2, C6.1, Q1.3 (C), R5.1, R11.1, R12.1
/P48_1_B: C5.1, Q1.1 (B), R1.2, R2.1
/P48_1_BC: Q2.3 (C), R2.2
/P48_2: C7.2, C8.1, Q3.3 (C), R10.1, R40.1, R41.1
/P48_2_B: C7.1, Q3.1 (B), R6.2, R7.1
/P48_2_BC: Q4.3 (C), R7.2
/PFL_IM: C67.2, R105.2, R106.2, U13.1 (IN-)
/PFL_IP: C68.2, R104.2, R107.2, U13.8 (IN+)
/PFL_ON: C68.1, R107.1, R109.1, U13.5 (OUT-)
/PFL_OP: C67.1, R106.1, R108.1, U13.4 (OUT+)
/PFR_IM: C76.2, R118.2, R119.2, U14.1 (IN-)
/PFR_IP: C77.2, R117.2, R120.2, U14.8 (IN+)
/PFR_ON: C77.1, R120.1, R122.1, U14.5 (OUT-)
/PFR_OP: C76.1, R119.1, R121.1, U14.4 (OUT+)
/PH48_1: J2.1, R3.1
/PH48_1_G: Q2.1 (B), R3.2, R4.1
/PH48_2: J2.3, R8.1
/PH48_2_G: Q4.1 (B), R8.2, R9.1
/PHL_DRV: K3.21, R104.1
/PHL_J: J11.T, K3.11
/PHL_LIN: K3.12, K3.22, R103.1
/PHL_R75: C66.1, K3.24, R102.2
/PHL_RFB: R99.1, R101.2, U12.2 (-)
/PHL_RG: C64.1, R99.2
/PHL_RIN: C63.1, K3.14, R97.1, R98.1
/PHL_RINS: R98.2, U12.3 (+)
/PHL_RN1: C65.2, R100.2, R101.1
/PHL_ROUT: C65.1, R100.1, R102.1, U12.1
/PHONO: J2.5, R123.1
/PHONO_D: D19.2 (A), R123.2
/PHONO_G: D19.1 (K), D20.1 (K), Q7.1 (G), R125.1
/PHONO_K: D21.2 (A), K3.A2, K4.A2, Q7.3 (D)
/PHR_DRV: K4.21, R117.1
/PHR_J: J12.T, K4.11
/PHR_LIN: K4.12, K4.22, R116.1
/PHR_R75: C75.1, K4.24, R115.2
/PHR_RFB: R112.1, R114.2, U12.6 (-)
/PHR_RG: C73.1, R112.2
/PHR_RIN: C72.1, K4.14, R110.1, R111.1
/PHR_RINS: R111.2, U12.5 (+)
/PHR_RN1: C74.2, R113.2, R114.1
/PHR_ROUT: C74.1, R113.1, R115.1, U12.7
/R2OK_G: Q9.1 (G), R218.2, R219.1
/R2_OK: J2.9, J3.2, R218.1
/RCAL_TIP: J25.T, K7.14
/RCAR_TIP: J26.T, K7.24
/SW_PHD: D20.2 (A), R124.2
/SW_PHONO: J28.2, R124.1
GND: C1.2, C2.1, C3.2, C4.1, C6.2, C8.2, C12.2, C13.2, C17.2, C18.2, C22.2, C23.2, C27.2, C28.2, C32.2, C33.2, C37.2, C38.2, C39.2, C40.2, C41.2, C42.2, C46.2, C47.2, C51.2, C52.2, C56.2, C57.2, C61.2, C62.2, C63.2, C64.2, C66.2, C70.2, C71.2, C72.2, C73.2, C75.2, C79.2, C80.2, C81.2, C82.2, C83.2, C84.2, C88.2, C89.2, C90.2, C91.2, C95.2, C96.2, C97.2, C98.2, C102.2, C103.2, C104.2, C105.2, C109.2, C110.2, C111.2, C112.2, C116.2, C117.2, C118.2, C119.2, C123.2, C124.2, C125.2, C126.2, C130.2, C131.2, C132.2, C133.2, C137.2, C138.2, C141.2, C142.2, C145.2, C146.2, D1.2 (A2), D4.2 (A2), D8.2 (A2), D11.2 (A2), J1.2, J1.4, J1.6, J1.8, J1.10, J2.2, J2.4, J2.6, J2.8, J2.10, J2.12, J2.14, J3.3, J4.3, J5.3, J5.4, J5.7, J5.8, J5.11, J5.12, J5.15, J5.16, J5.19, J5.20, J5.23, J5.24, J5.27, J5.28, J5.31, J5.32, J5.35, J5.36, J5.39, J5.40, J6.3, J6.4, J6.7, J6.8, J6.11, J6.12, J6.15, J6.16, J6.19, J6.20, J6.23, J6.24, J6.27, J6.28, J6.31, J6.32, J6.35, J6.36, J6.39, J6.40, J6.43, J6.44, J7.1, J7.G, J7.S, J8.1, J8.G, J8.S, J9.S, J10.S, J11.S, J12.S, J13.S, J14.S, J15.S, J16.S, J17.S, J18.S, J19.S, J20.S, J21.S, J22.S, J23.S, J24.S, J25.S, J26.S, J27.1, J27.2, J28.3, Q2.2 (E), Q4.2 (E), Q5.2 (S), Q6.2 (S), Q7.2 (S), Q9.2 (S), R4.2, R5.2, R9.2, R10.2, R15.2, R18.2, R19.2, R22.2, R24.2, R44.2, R47.2, R48.2, R51.2, R53.2, R69.2, R71.2, R74.1, R80.1, R86.1, R92.1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

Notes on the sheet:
R1 -> A1: 18 differential ADC pairs (FS 8 Vrms diff into the AN0635 buffers), A1 -> R1: 4 DAC pairs; phantom per channel and phono/line from R2 (R118); output relays need MUTE and R2_OK (R137)
Level plan in design.py: every input -> differential pair, FS 2 Vrms diff, to the Cirrus buffers on A1
Rev 0.1: schematic only; jacks vertical-mount Neutrik NCJ6FI-V, NJ3FD-V; RCA part to choose

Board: 4 copper layers, 462 parts (435 on the bottom side), 269 nets, no tracks yet.

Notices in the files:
hardware/r1-audio/gen/design.py:
License: CERN-OHL-S-2.0 (hardware data), AGPL-3.0-or-later (code).
hardware/r1-audio/r1-audio.kicad_pcb:
Shtuka Druka - open hardware, CERN-OHL-S-2.0
Shtuka Druka CERN-OHL-S-2.0
